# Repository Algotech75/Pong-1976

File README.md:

# Pong-1976
Pong, based on the AY-3-8500 chip - KiCAD PCB 

## Schéma pompé

## PCB

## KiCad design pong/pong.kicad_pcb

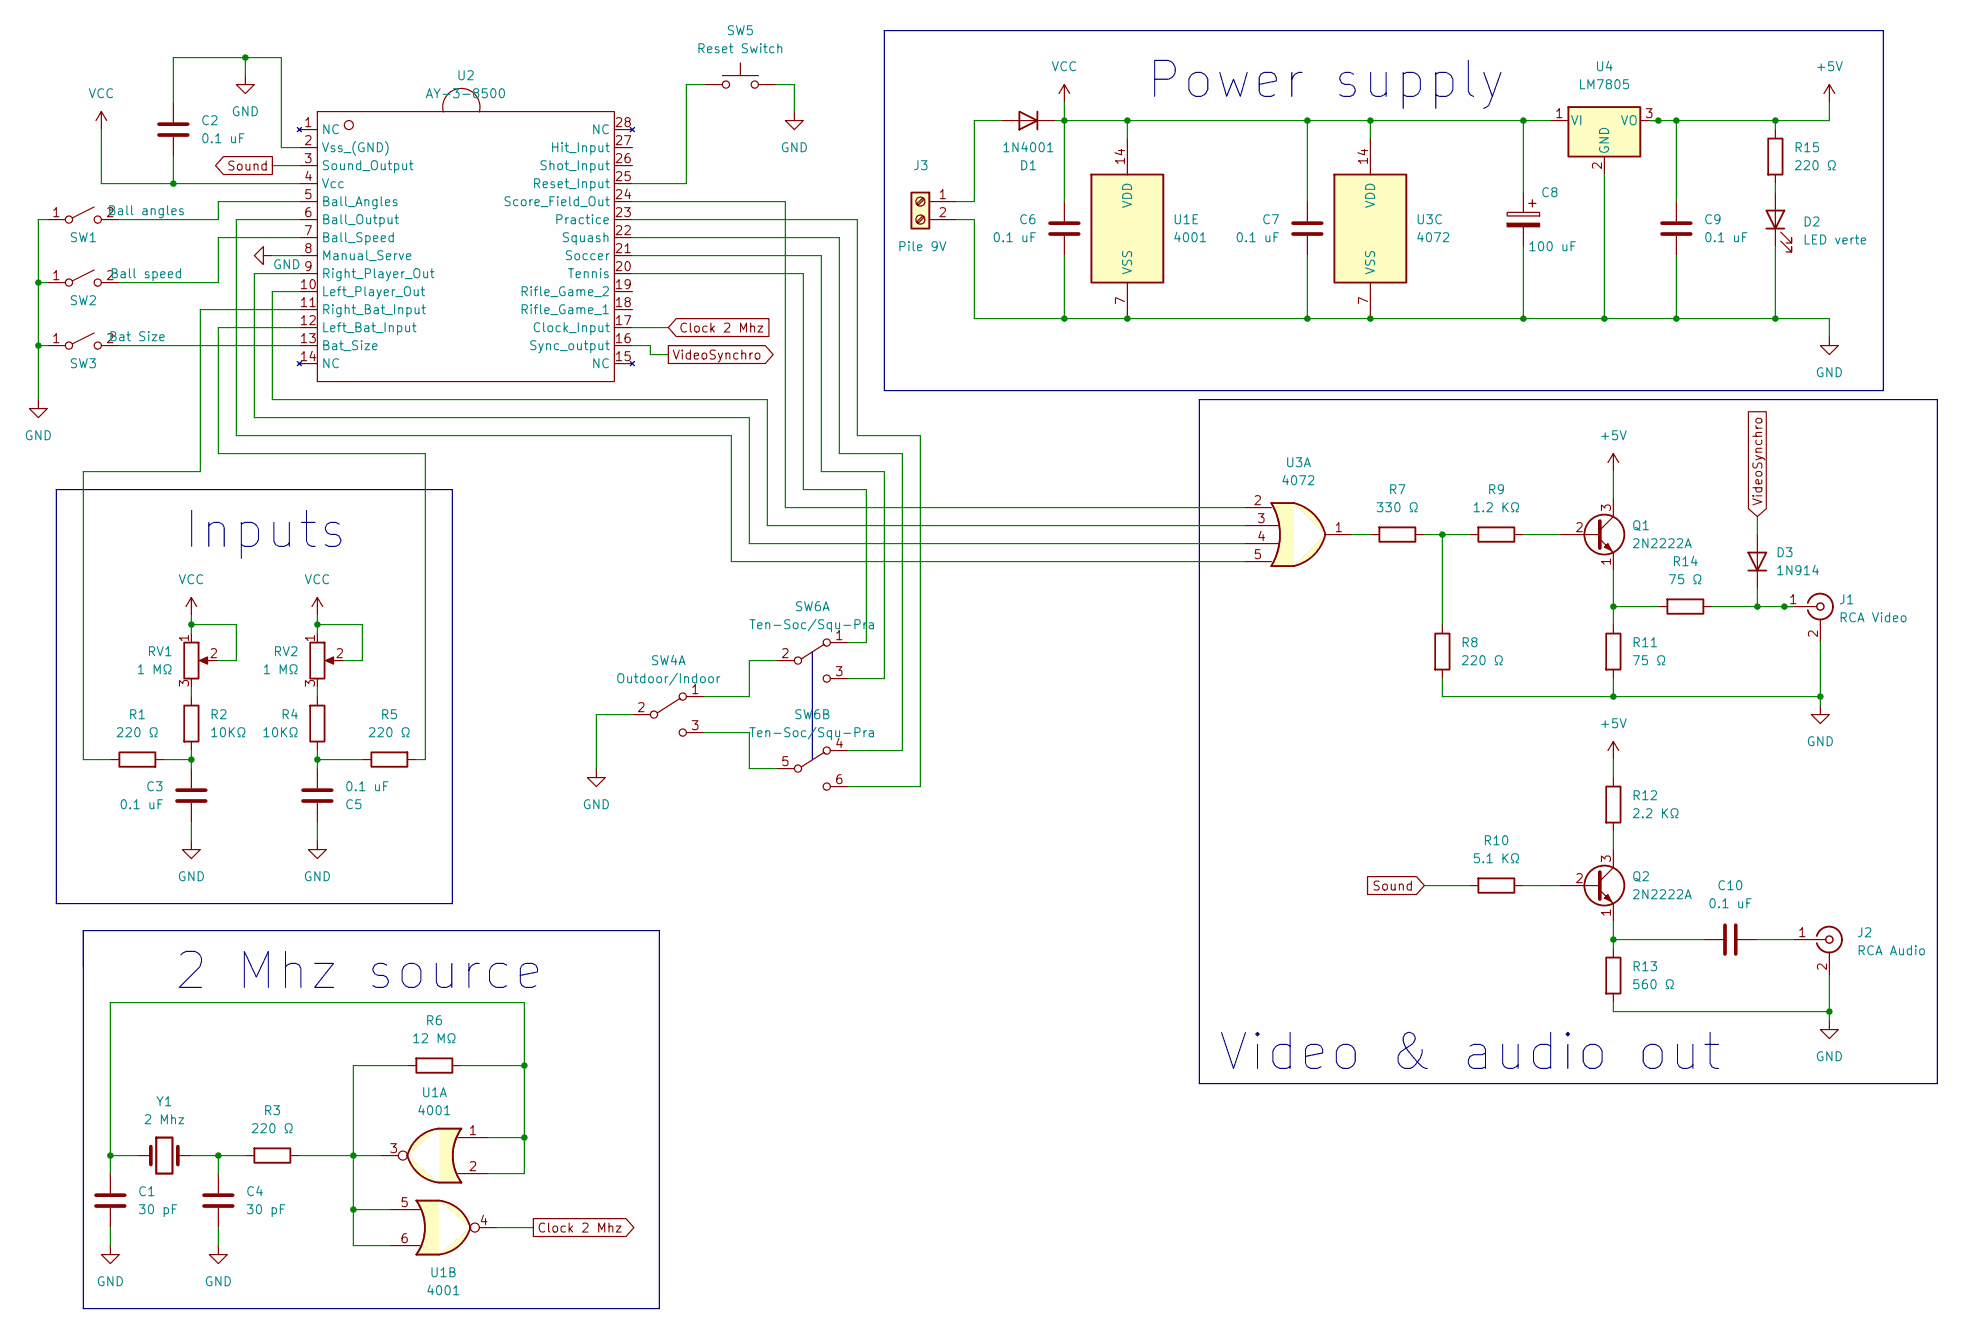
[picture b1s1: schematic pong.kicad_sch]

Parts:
C1, C4: 30 pF; C_Disc_D3.4mm_W2.1mm_P2.50mm
C2, C3, C5, C6, C7, C9, C10: 0.1 uF; C_Rect_L7.2mm_W3.0mm_P5.00mm_FKS2_FKP2_MKS2_MKP2
C8: 100 uF; CP_Radial_D6.3mm_P2.50mm
D1: 1N4001; D_DO-41_SOD81_P7.62mm_Horizontal
D2: LED verte; LED_D5.0mm_Clear
D3: 1N914; D_DO-35_SOD27_P7.62mm_Horizontal
J1: RCA Video; RCA
J2: RCA Audio; RCA
J3: Pile 9V; TerminalBlock_Phoenix_MKDS-1,5-2-5.08_1x02_P5.08mm_Horizont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
Q1, Q2: 2N2222A; TO-92_Inline
R1, R3, R5, R8, R15: 220 Ω; R_Axial_DIN0207_L6.3mm_D2.5mm_P7.62mm_Horizontal
R2, R4: 10KΩ; R_Axial_DIN0207_L6.3mm_D2.5mm_P7.62mm_Horizontal
R6: 12 MΩ; R_Axial_DIN0207_L6.3mm_D2.5mm_P7.62mm_Horizontal
R7: 330 Ω; R_Axial_DIN0207_L6.3mm_D2.5mm_P7.62mm_Horizontal
R9: 1.2 KΩ; R_Axial_DIN0207_L6.3mm_D2.5mm_P7.62mm_Horizontal
R10: 5.1 KΩ; R_Axial_DIN0207_L6.3mm_D2.5mm_P7.62mm_Horizontal
R11, R14: 75 Ω; R_Axial_DIN0207_L6.3mm_D2.5mm_P7.62mm_Horizontal
R12: 2.2 KΩ; R_Axial_DIN0207_L6.3mm_D2.5mm_P7.62mm_Horizontal
R13: 560 Ω; R_Axial_DIN0207_L6.3mm_D2.5mm_P7.62mm_Horizontal
RV1, RV2: 1 MΩ; TerminalBlock_Phoenix_MKDS-1,5-3-5.08_1x03_P5.08mm_Horizont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
SW1: Ball angles; SW_E-Switch_EG1271_DPDT
SW2: Ball speed; SW_E-Switch_EG1271_DPDT
SW3: Bat Size; SW_E-Switch_EG1271_DPDT
SW4: Outdoor/Indoor; SW_E-Switch_EG1271_DPDT
SW5: Reset Switch; SW_PUSH_6mm_H5mm
SW6: Ten-Soc/Squ-Pra; SW_E-Switch_EG1271_DPDT
U1: 4001; DIP-14_W7.62mm_Socket_LongPads
U2: AY-3-8500; DIP-28_W15.24mm_Socket_LongPads
U3: 4072; DIP-14_W7.62mm_Socket_LongPads
U4: LM7805; TO-220-3_Vertical
Y1: 2 Mhz; Crystal_HC49-4H_Vertical

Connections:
+5V: C9.1, Q1.3 (C), R12.1, R15.1, U4.3 (VO)
Clock 2 Mhz: U1.4, U2.17 (Clock_Input)
GND: C1.2, C2.1, C3.1, C4.2, C5.2, C6.1, C7.1, C8.2, C9.2, D2.1 (K), J1.2 (Ext), J2.2 (Ext), J3.2, R8.2, R11.2, R13.2, SW1.1 (A), SW2.1 (A), SW3.1 (A), SW4.2 (B), SW5.2, U1.7 (VSS), U2.2 (Vss_(GND)), U2.8 (Manual_Serve), U3.7 (VSS), U4.2 (GND)
unnamed: C1.1, R6.1, U1.1, U1.2, Y1.1
unnamed: C3.2, R1.2, R2.2
unnamed: C4.1, R3.2, Y1.2
unnamed: C5.1, R4.1, R5.1
unnamed: C10.1, J2.1 (In)
unnamed: C10.2, Q2.1 (E), R13.1
unnamed: D1.2 (A), J3.1
unnamed: D2.2 (A), R15.2
unnamed: D3.1 (K), J1.1 (In), R14.1
unnamed: Q1.1 (E), R11.1, R14.2
unnamed: Q1.2 (B), R9.1
unnamed: Q2.2 (B), R10.1
unnamed: Q2.3 (C), R12.2
unnamed: R1.1, U2.11 (Right_Bat_Input)
unnamed: R2.1, RV1.3
unnamed: R3.1, R6.2, U1.3, U1.5, U1.6
unnamed: R4.2, RV2.3
unnamed: R5.2, U2.12 (Left_Bat_Input)
unnamed: R7.1, R8.1, R9.2
unnamed: R7.2, U3.1
unnamed: SW1.2 (B), U2.5 (Ball_Angles)
unnamed: SW2.2 (B), U2.7 (Ball_Speed)
unnamed: SW3.2 (B), U2.13 (Bat_Size)
unnamed: SW4.1 (A), SW6.2 (B)
unnamed: SW4.3 (C), SW6.5 (B)
unnamed: SW5.1, U2.25 (Reset_Input)
unnamed: SW6.1 (A), U2.20 (Tennis)
unnamed: SW6.3 (C), U2.21 (Soccer)
unnamed: SW6.4 (A), U2.22 (Squash)
unnamed: SW6.6 (C), U2.23 (Practice)
unnamed: U2.6 (Ball_Output), U3.5
unnamed: U2.9 (Right_Player_Out), U3.4
unnamed: U2.10 (Left_Player_Out), U3.3
unnamed: U2.24 (Score_Field_Out), U3.2
Sound: R10.2, U2.3 (Sound_Output)
VCC: C2.2, C6.2, C7.2, C8.1, D1.1 (K), RV1.1, RV1.2, RV2.1, RV2.2, U1.14 (VDD), U2.4 (Vcc), U3.14 (VDD), U4.1 (VI)
VideoSynchro: D3.2 (A), U2.16 (Sync_output)

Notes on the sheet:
Video & audio out
Power supply
Inputs
2 Mhz source

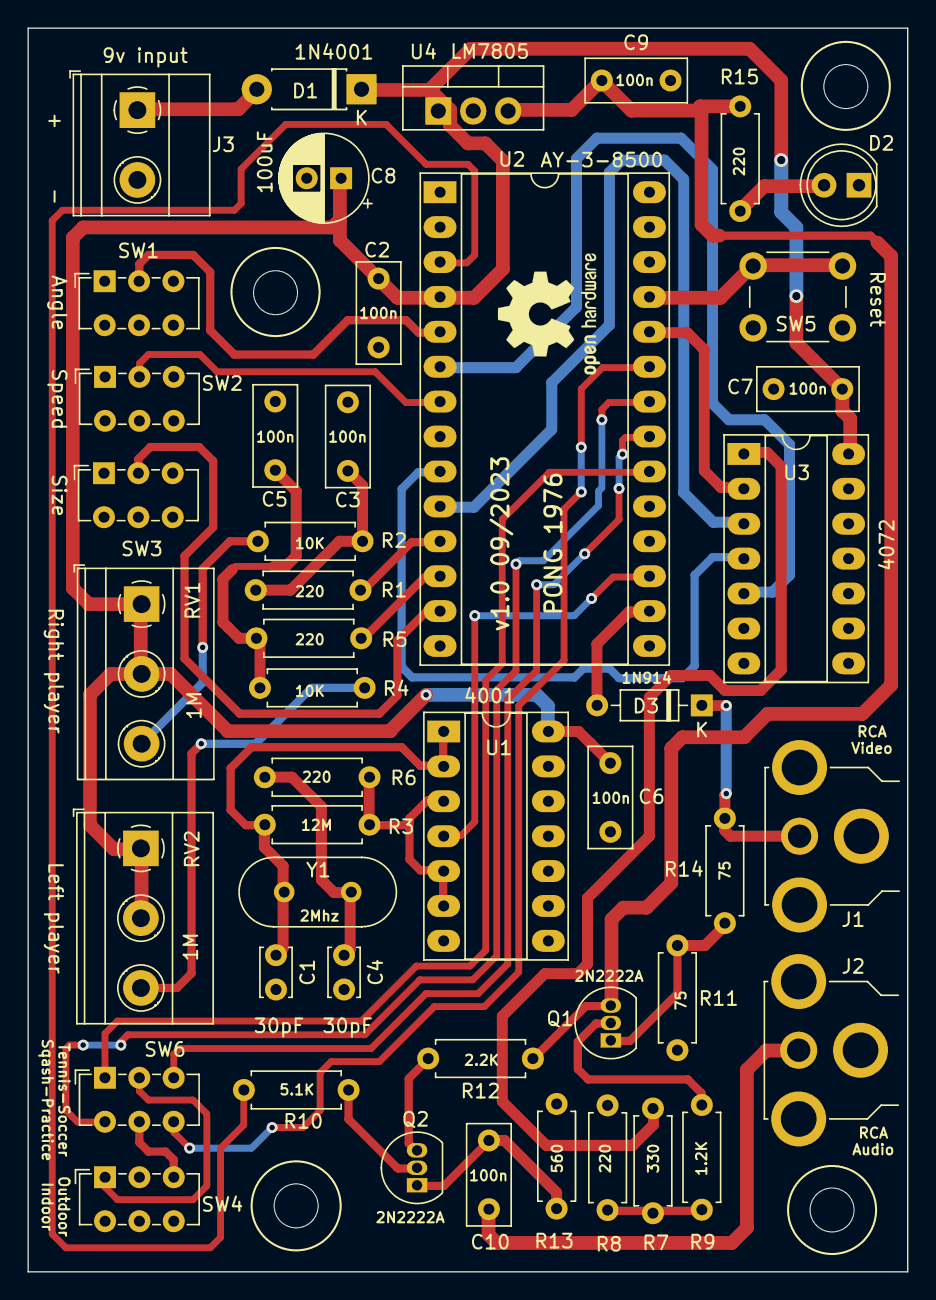
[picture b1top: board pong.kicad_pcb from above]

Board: 2 copper layers, 64.0 x 90.5 mm, 51 parts (0 on the bottom side), 40 nets.

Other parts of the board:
HOLE1, HOLE2, HOLE3, HOLE4: MountingHole_3.2mm_M3
REFLOGO: OSHW-Logo2_9.8x8mm_SilkScreen

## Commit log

2023-10-10 1st commit
